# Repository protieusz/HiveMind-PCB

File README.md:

# HiveMind-PCB
HiveMind "Untested" PCB version that was converted from the handwired version. 47 Keys QAZ-ish layout with a numpad in the center and fits a 60% keyboard travel case.
Please print at your own risk.  No support will be given.  Pcb was designed using EasyEDA and DRC shows no errors.  MCU used is the Pimoroni PGA2040. Routing is auto routed. Have fun and good luck.

UPDATE: May 7, 2023: Rev 2 gerbers uploaded and delete Rev 1.  Rev 1 had a mcu footprint center cut out that will render the pcb useless when using auto routing for traces.  Use Rev 2 gerbers but gerbers are still un-tested. Please print at your own risk!!!

2D view of the top pcb

2D view of the bottom pcb

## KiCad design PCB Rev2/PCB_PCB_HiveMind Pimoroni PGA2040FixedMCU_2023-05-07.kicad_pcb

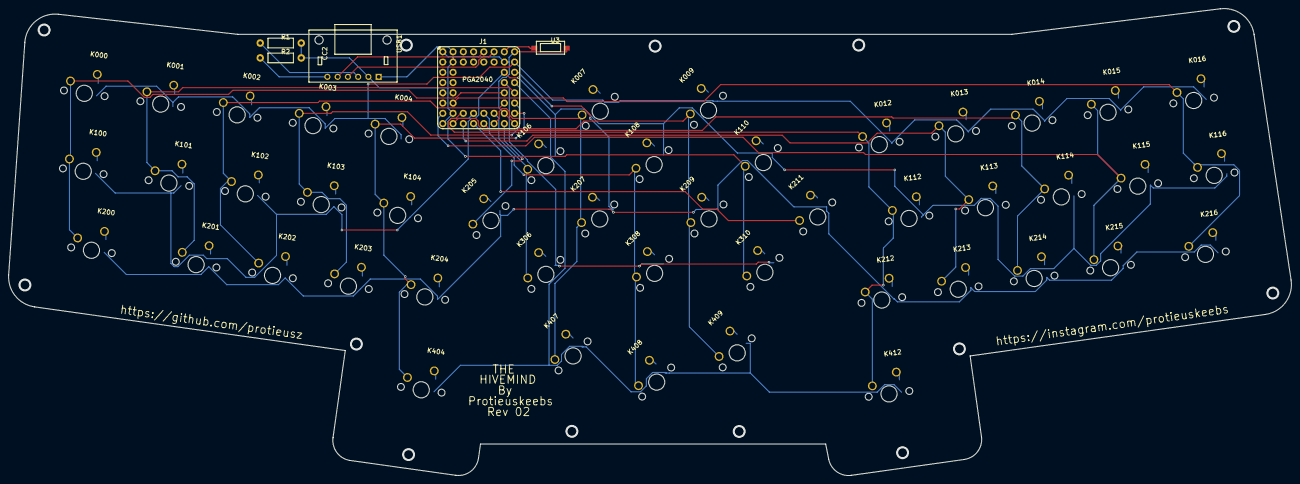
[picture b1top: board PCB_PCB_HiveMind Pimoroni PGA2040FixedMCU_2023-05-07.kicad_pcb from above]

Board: 2 copper layers, 317.6 x 115.6 mm, 99 parts (0 on the bottom side), 76 nets.

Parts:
D000, D001, D002, D003, D004, D007, D009, D012, D013, D014, D015, D016, D100, D101, D102, D103, D104, D106, D108, D110, D112, D113, D114, D115, D116, D200, D201, D202, D203, D204, D205, D207, D209, D211, D212, D213, D214, D215, D216, D306, D308, D310, D404, D407, D408, D409, D412: DIODE-SOD123
J1: PGA2040; gge34507
K000, K001, K002, K003, K004, K007, K009, K012, K013, K014, K015, K016, K100, K101, K102, K103, K104, K106, K108, K110, K112, K113, K114, K115, K116, K200, K201, K202, K203, K204, K205, K207, K209, K211, K212, K213, K214, K215, K216, K306, K308, K310, K404, K407, K408, K409, K412: 100; CHERRY_MX_100_MILLMAX
R1, R2: 5.1KΩ(5101); AXIAL-0.4
U3: RESET SWITCH
USB1: CC2; USB-C_TH_BREAKOUT_6P

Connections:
COL0: J1.E7, K000.2, K100.2, K200.2
COL1: J1.E8, K001.2, K101.2, K201.2
COL2: J1.F7, K002.2, K102.2, K202.2
COL3: J1.F8, K003.2, K103.2, K203.2
COL4: J1.G8, K004.2, K104.2, K204.2, K404.2
COL5: J1.H7, K205.2
COL6: J1.G6, K106.2, K306.2
COL7: J1.H6, K007.2, K207.2, K407.2
COL8: J1.G5, K108.2, K308.2, K408.2
COL9: J1.H5, K009.2, K209.2, K409.2
COL10: J1.G4, K110.2, K310.2
COL11: J1.H4, K211.2
COL12: J1.G3, K012.2, K112.2, K212.2, K412.2
COL13: J1.H3, K013.2, K113.2, K213.2
COL14: J1.H2, K014.2, K114.2, K214.2
COL15: J1.G1, K015.2, K115.2, K215.2
COL16: J1.F2, K016.2, K116.2, K216.2
D000_A: D000.A, K000.1
D003_A: D003.A, K003.1
D009_A: D009.A, K009.1
D013_A: D013.A, K013.1
D014_A: D014.A, K014.1
D016_A: D016.A, K016.1
D101_A: D101.A, K101.1
D102_A: D102.A, K102.1
D104_A: D104.A, K104.1
D106_A: D106.A, K106.1
D110_A: D110.A, K110.1
D112_A: D112.A, K112.1
D115_A: D115.A, K115.1
D201_A: D201.A, K201.1
D202_A: D202.A, K202.1
D204_A: D204.A, K204.1
D205_A: D205.A, K205.1
D207_A: D207.A, K207.1
D211_A: D211.A, K211.1
D212_A: D212.A, K212.1
D215_A: D215.A, K215.1
D308_A: D308.A, K308.1
D408_A: D408.A, K408.1
D412_A: D412.A, K412.1
D+: J1.A5, USB1.3
D-: J1.A6, USB1.2
GND: J1.A1, J1.A8, J1.B2, J1.B7, J1.G2, J1.G7, J1.H1, J1.H8, R1.2, R2.2, U3.2, USB1.6
K001_1: D001.A, K001.1
K002_1: D002.A, K002.1
K004_1: D004.A, K004.1
K007_1: D007.A, K007.1
K012_1: D012.A, K012.1
K015_1: D015.A, K015.1
K100_1: D100.A, K100.1
K103_1: D103.A, K103.1
K108_1: D108.A, K108.1
K113_1: D113.A, K113.1
K114_1: D114.A, K114.1
K116_1: D116.A, K116.1
K200_1: D200.A, K200.1
K203_1: D203.A, K203.1
K209_1: D209.A, K209.1
K213_1: D213.A, K213.1
K214_1: D214.A, K214.1
K216_1: D216.A, K216.1
K306_1: D306.A, K306.1
K310_1: D310.A, K310.1
K404_1: D404.A, K404.1
K407_1: D407.A, K407.1
K409_1: D409.A, K409.1
ROW0: D000.C, D001.C, D002.C, D003.C, D004.C, D007.C, D009.C, D012.C, D013.C, D014.C, D015.C, D016.C, J1.B8
ROW1: D100.C, D101.C, D102.C, D103.C, D104.C, D106.C, D108.C, D110.C, D112.C, D113.C, D114.C, D115.C, D116.C, J1.C7
ROW2: D200.C, D201.C, D202.C, D203.C, D204.C, D205.C, D207.C, D209.C, D211.C, D212.C, D213.C, D214.C, D215.C, D216.C, J1.C8
ROW3: D306.C, D308.C, D310.C, J1.D7
ROW4: D404.C, D407.C, D408.C, D409.C, D412.C, J1.D8
RST: J1.A7, U3.1
USB1_4: R1.1, USB1.4
USB1_5: R2.1, USB1.5
VCC: J1.A2, USB1.1

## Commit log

2023-05-01 Add gerbers, schematic & pcb Kicad converted
2023-05-01 Add KLE
2023-05-01 Add description and add pics
2023-05-01 Add ProtieusKeebs Logo
2023-05-08 Fix mcu cut out
2023-05-08 Add kicad converted files for Rev 2
2023-05-08 Update with Rev 2 gerber changes
